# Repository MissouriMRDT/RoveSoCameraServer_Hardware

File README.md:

# RoveSoCameraServer

This is the repository for a custom camera server using a Jetson Xavier NX and the GMSL2 protocol.

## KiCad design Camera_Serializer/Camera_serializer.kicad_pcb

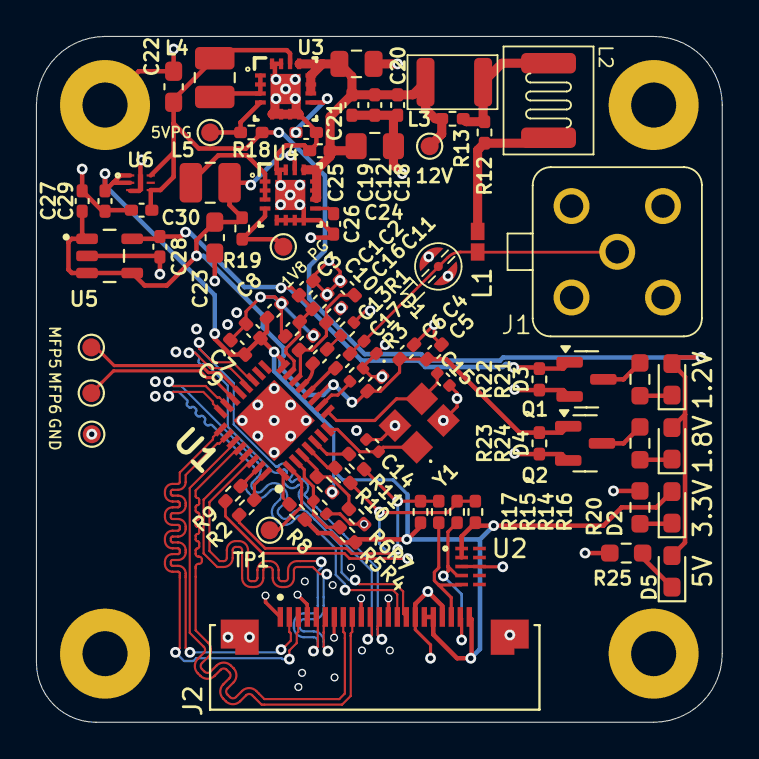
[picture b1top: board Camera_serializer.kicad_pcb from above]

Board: 4 copper layers, 38.1 x 38.1 mm, 88 parts (0 on the bottom side), 52 nets.

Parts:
C1, C4, C7, C16, C18: 10n; C_0402_1005Metric_Pad0.74x0.62mm_HandSolder
C2, C5, C8, C10, C12, C13, C17: 100n; C_0402_1005Metric_Pad0.74x0.62mm_HandSolder
C3, C6, C9, C11: 10u; C_0402_1005Metric_Pad0.74x0.62mm_HandSolder
C14, C15: 13pF; C_0402_1005Metric
C19, C25: 0.1uF; C_0402_1005Metric_Pad0.74x0.62mm_HandSolder
C20: 10uF; C_0805_2012Metric
C21, C26: 3.3nF; C_0402_1005Metric_Pad0.74x0.62mm_HandSolder
C22, C23: 22uF; C_0603_1608Metric_Pad1.08x0.95mm_HandSolder
C24: 10uF; C_0805_2012Metric_Pad1.18x1.45mm_HandSolder
C27, C28, C29, C30: 1uF; C_0402_1005Metric_Pad0.74x0.62mm_HandSolder
D1: D_0402_1005Metric
D2, D3, D4, D5: GREEN; LED_0603_1608Metric_Pad1.05x0.95mm_HandSolder
H1, H2, H3, H4: MountingHole_Pad; MountingHole_2.5mm_Pad
J1: RF55-28Z-T-00-50-G-SH
J2: F32Q-1A7H1-11022
L1: 560n; PFL1609-561MEW
L2: 6u8; 1812PS-682JRC
L3: 22u; SRN3015C-220M
L4, L5: 2.2uH; L_1008_2520Metric
Q1, Q2: BSS138; SOT-23
R1: 49.9; R_0402_1005Metric
R2, R9, R10, R11: 0R; R_0402_1005Metric_Pad0.72x0.64mm_HandSolder
R3: 402; R_0402_1005Metric
R4, R7: R_0402_1005Metric_Pad0.72x0.64mm_HandSolder
R5: 10k; R_0402_1005Metric
R6: 10k; R_0402_1005Metric_Pad0.72x0.64mm_HandSolder
R8: 10K; R_0402_1005Metric_Pad0.72x0.64mm_HandSolder
R12, R13: 5k; R_0402_1005Metric_Pad0.72x0.64mm_HandSolder
R14, R15: 100; R_0402_1005Metric_Pad0.72x0.64mm_HandSolder
R16, R17: 4k7; R_0402_1005Metric_Pad0.72x0.64mm_HandSolder
R18, R19, R22, R23: 100k; R_0402_1005Metric_Pad0.72x0.64mm_HandSolder
R20: 330; R_0603_1608Metric_Pad0.98x0.95mm_HandSolder
R21, R24, R25: 820; R_0603_1608Metric_Pad0.98x0.95mm_HandSolder
T1: Coax Testpoint
TP1, TP2, TP3, TP4, TP5, TP7, TP8: TestPoint; TestPoint_Pad_D1.0mm
U1: QFN50P500X500X80-33N
U2: PUSB3FR4Z
U3: TPS62133RGTR
U4: TPS62131RGTT; TPS62133RGTR
U5: TPS73601DBVR
U6: MIC5528-3.3YMT-TR; TDFN6_1P2X1P2_MCH
Y1: EB2532YA08-25.000M_TR

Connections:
+1V2: C1.1, C2.1, C3.1, C28.1, Q1.1 (G), R22.1, U1.15 (VDD), U5.5 (OUT)
+1V8: C4.1, C5.1, C6.1, C23.1, C27.1, L5.2, Q2.1 (G), R19.1, R23.1, U1.11 (VDD18), U4.14 (VOS), U5.1 (IN), U5.3 (EN), U5.4 (NR/FB)
+3V3: C7.1, C8.1, C9.1, C29.1, D2.2 (A), J2.17, J2.18, J2.22, R4.2, R6.1, R8.1, R16.2, R17.2, U1.16 (VDDIO), U2.1, U2.2, U6.1 (VOUT), U6.2 (VOUT)
+5V: C22.1, C30.1, D3.2 (A), D4.2 (A), D5.2 (A), L4.2, R18.1, U3.14 (VOS), U6.4 (EN), U6.6 (VIN)
+12V: C12.1, C18.1, C19.1, C20.1, C24.1, C25.1, L3.2, R13.1, TP4.1, U3.10 (AVIN), U3.11 (PVIN), U3.12 (PVIN), U3.13 (EN), U4.10 (AVIN), U4.11 (PVIN), U4.12 (PVIN), U4.13 (EN)
/GMSL_Connector/SIOP_COAX: C17.2, D1.2, J1.1, L1.1, T1.1
/csi/CAM_SCL: J2.20, R15.1, U2.5
/csi/CAM_SDA: J2.21, R14.1, U2.4
/csi/CSI.CK_N: J2.8, U1.28 (CKN)
/csi/CSI.CK_P: J2.9, U1.27 (CKP)
/csi/CSI.D0_N: J2.2, U1.26 (D0N)
/csi/CSI.D0_P: J2.3, U1.25 (D0P)
/csi/CSI.D1_N: J2.5, U1.30 (D1N)
/csi/CSI.D1_P: J2.6, U1.29 (D1P)
/csi/CSI.D2_N: J2.11, U1.20 (D2N)
/csi/CSI.D2_P: J2.12, U1.19 (D2P)
/csi/CSI.D3_N: J2.14, U1.24 (D3N)
/csi/CSI.D3_P: J2.15, U1.23 (D3P)
/csi/I2C.SCL: R2.2, R11.2, R15.2, R17.1
/csi/I2C.SDA: R9.2, R10.2, R14.2, R16.1
/serializer/CFG0: R4.1, R5.2, U1.3 (MFP1/CFG0)
/serializer/CFG1: R6.2, R7.1, U1.4 (MFP2/CFG1)
/serializer/PWDN: R8.2, U1.1 (PWDNB)
/serializer/X1: C14.1, U1.8 (X1/OSC), Y1.1
/serializer/X2: C15.1, U1.9 (X2), Y1.3
/serializer/XRES: R3.2, U1.10 (XRES)
GND: C1.2, C2.2, C3.2, C4.2, C5.2, C6.2, C7.2, C8.2, C9.2, C10.2, C11.2, C12.2, C14.2, C15.2, C16.2, C18.2, C19.2, C20.2, C21.2, C22.2, C23.2, C24.2, C25.2, C26.1, C27.2, C28.2, C29.2, C30.2, D1.1, H1.1, H2.1, H3.1, H4.1, J1.2, J2.1, J2.4, J2.7, J2.10, J2.13, J2.16, J2.19, J2.SH1, J2.SH2, Q1.2 (S), Q2.2 (S), R1.2, R3.1, R5.1, R7.2, R20.2, R22.2, R23.2, R25.2, T1.2, TP8.1, U1.33 (GND), U2.3, U2.8, U3.5 (FB), U3.6 (AGND), U3.7 (FSW), U3.8 (DEF), U3.15 (PGND), U3.16 (PGND), U3.17 (EP), U4.5 (FB), U4.6 (AGND), U4.7 (FSW), U4.8 (DEF), U4.15 (PGND), U4.16 (PGND), U4.17 (EP), U5.2 (GND), U6.3 (GND), U6.7 (EPAD), Y1.2, Y1.4
unnamed: C13.1, R1.1
unnamed: D2.1 (K), R20.1
unnamed: D3.1 (K), R21.1
unnamed: D4.1 (K), R24.1
unnamed: D5.1 (K), R25.1
unnamed: L1.2, L2.1, R12.2
unnamed: L2.2, L3.1, R12.1, R13.2
unnamed: L4.1, U3.1 (SW), U3.2 (SW), U3.3 (SW)
unnamed: L5.1, U4.1 (SW), U4.2 (SW), U4.3 (SW)
unnamed: Q1.3 (D), R21.2
unnamed: Q2.3 (D), R24.2
unnamed: C10.1, C11.1, C16.1, U1.14 (CAP_VDD)
unnamed: TP1.1, U1.2 (MFP0)
unnamed: TP2.1, U1.21 (MFP5)
unnamed: TP3.1, U1.22 (MFP6)
unnamed: R9.1, U1.31 (MFP7)
unnamed: R2.1, U1.32 (MFP8)
unnamed: R10.1, U1.5 (MFP9)
unnamed: R11.1, U1.6 (MFP10)
unnamed: C13.2, U1.13 (SION)
unnamed: C17.1, U1.12 (SIOP)
unnamed: R18.2, TP5.1, U3.4 (PG)
unnamed: C21.1, U3.9 (SS_TR)
unnamed: R19.2, TP7.1, U4.4 (PG)
unnamed: C26.2, U4.9 (SS_TR)

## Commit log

2024-10-29 Initial project setup
2024-10-30 Added SODIMM connector for Jetson
2024-11-02 Added camera serializer and libraries
2024-11-02 Added serializer schematic and fakra connector
2024-11-16 Added crystal and capacitor, plus config resistors
2024-11-25 Basic setup of main SOC done, working on POC circuit now.
2024-11-29 Finished POC circuit and added TVS diode
2024-12-26 Added CSI connector
2024-12-26 Added tvs diodes
2024-12-26 Finished CSI interface
2024-12-28 Added 5V buck
2024-12-28 Finished power converters
2024-12-29 Finishe schematic
2024-12-29 Layout started
2024-12-30 Switched out 1.2V LDO for better one
2025-01-02 All components placed in correct positions
2025-01-02 Routed most traces except CSI lines
2025-01-04 Finished routing
2025-01-25 Finished differential routing
2025-01-28 Fixed power IC disconnected on schematic
2025-01-29 Finished Rev1
2025-10-25 Updated to Kicad 9 and added datasheet for 22uH inductor
2025-11-04 Added buck simulation
2025-11-04 Add 5V buck converter and update gitignore
2025-11-04 Remove huge files
2026-03-24 Final hardware as of order
2026-03-27 Added simulation
